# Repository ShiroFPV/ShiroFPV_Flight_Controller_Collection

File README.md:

# ShiroFPV Flight Controller Collection

Open-source FPV flight controller hardware — schematic, PCB layout, symbols and
firmware target, all published in full.

Designed in KiCad, targeted at Betaflight, and licensed so it stays open.

More at **[shirofpv.com/flight-controller](https://shirofpv.com/flight-controller)**

## Boards

| Board | Size | MCU | Analog OSD | Status |
|---|---|---|---|---|
| [**V1** `SFVPF435`](V1_30x30_SFVPF435/) | 30.5 × 30.5 | AT32F435RGT7 | ✅ AT7456 | Released |
| [**V2** `SFVPF435`](V2_20x20_SFVPF435/) | 20.5 × 20.5 | AT32F435, 48-pin | ❌ digital only | 🚧 In development |

---

## V1 — `SFVPF435` (30.5 × 30.5)

| | |
|---|---|
| **MCU** | Artery AT32F435RGT7, up to 288 MHz |
| **Gyro** | ICM-20602 |
| **Baro** | BME280 |
| **OSD** | AT7456 |
| **Blackbox** | 16 Mb onboard flash |
| **USB** | USB-C |
| **Mount** | 30.5 × 30.5 mm standard stack |
| **Firmware** | Betaflight |

### Layout

```
V1_30x30_SFVPF435/
├─ Shematic/          hardware sources — CERN-OHL-S v2
│  ├─ ShiroFPV_Flight_Controller.kicad_sch    schematic
│  ├─ ShiroFPV_Flight_Controller.kicad_pcb    PCB layout
│  ├─ All_Own_Symbols.kicad_sym               custom symbols
│  ├─ All_Own_Symbols.pretty/                 custom footprints
│  └─ .glb                                    3D model
└─ Release/           firmware — GPL-3.0-or-later
   ├─ config.h                                Betaflight target config
   └─ SFPVF435V1.hex                          compiled firmware
```

> Note: `Shematic/` is a typo for `Schematic/` kept as-is so existing links and
> clones don't break.

---

## V2 — `SFVPF435` (20 × 20) — coming soon

A smaller board for builds a 30.5 stack won't fit. Decided so far:

| | |
|---|---|
| **MCU** | AT32F435, 48-pin package |
| **Mount** | 20 × 20 mm |
| **Analog OSD** | none — digital video only |
| **Firmware** | Betaflight |

Dropping the analog OSD chip is what buys the space. Everything else — gyro,
baro, blackbox, UART count, power stage — is still being worked out.

Details in [`V2_20x20_SFVPF435/`](V2_20x20_SFVPF435/).

---

## Datasheets

Artery's documentation is not redistributed here — it is their copyright.
Download it from the source:

- **AT32F435** — [product page](https://www.arterychip.com/en/product/AT32F435.jsp)
  (datasheet + reference manual)
- **AT32F437** — [product page](https://www.arterychip.com/en/product/AT32F437.jsp)

---

## Building one

The design files are complete — schematic, layout, custom symbols and
footprints. Open `ShiroFPV_Flight_Controller.kicad_pro` in KiCad 8 or newer,
export gerbers, and send them to whichever fab you like.

Flash `SFPVF435V1.hex` with the Betaflight Configurator, or build from the
Betaflight sources using `config.h` as the target definition.

It flies. Mostly.

---

## Licence

Two licences, because there are two kinds of work here. Both copyleft.

| Part | Licence |
|---|---|
| Hardware design (`Shematic/`) | [CERN-OHL-S v2](LICENSE) |
| Firmware (`Release/`) | [GPL-3.0-or-later](V1_30x30_SFVPF435/Release/LICENSE) |

**Short version:** use it, modify it, build it, sell it. If you distribute a
modified version, publish your sources under the same licence. You can profit
from this design — you just can't close it.

Full detail and reasoning in **[LICENSING.md](LICENSING.md)**.

---

## Contributing

Issues and pull requests welcome — improvements, fixes, or a revision of your
own. Contributions are accepted under the same licences as above.

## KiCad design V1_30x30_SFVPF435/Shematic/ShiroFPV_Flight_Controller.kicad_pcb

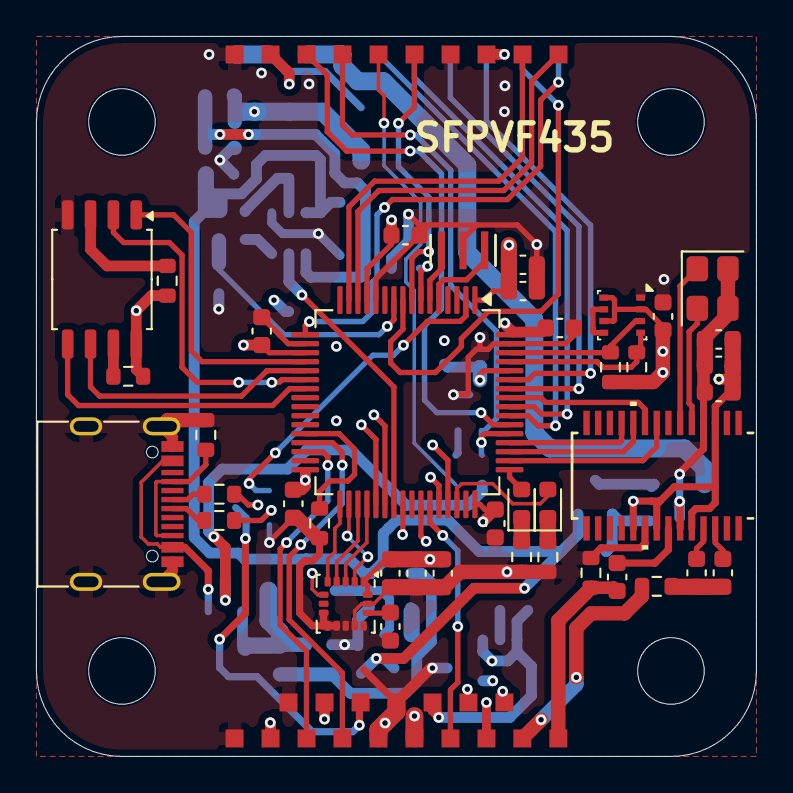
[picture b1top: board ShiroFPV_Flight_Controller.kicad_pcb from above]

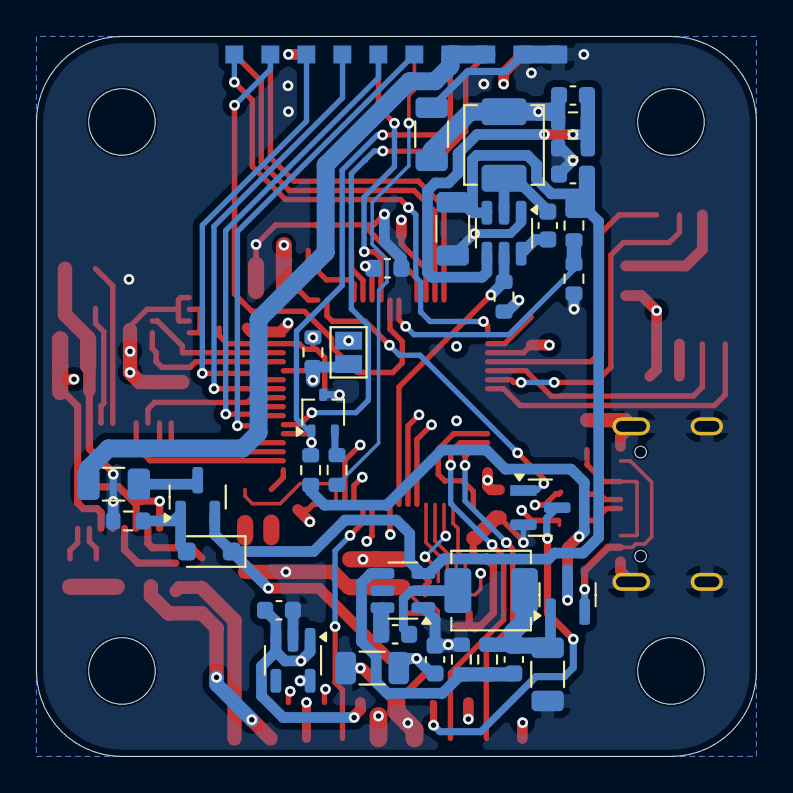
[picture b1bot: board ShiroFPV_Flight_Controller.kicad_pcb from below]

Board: 4 copper layers, 40.0 x 40.0 mm, 112 parts (45 on the bottom side), 79 nets.

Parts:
C1, C2, C4, C6, C7, C10, C11, C12, C13, C15, C16, C20, C23, C25, C26, C27, C28, C29: 100nF; C_0603_1608Metric
C3: 10nF; C_0603_1608Metric
C5, C31: 1uF; C_0603_1608Metric
C8, C9: 47uF; C_0603_1608Metric
C14, C38: 10uF; C_1206_3216Metric
C17: 100pF; C_0603_1608Metric
C18, C19: 47uF; C_1206_3216Metric
C22: 150pF; C_0603_1608Metric
C32: CSTCE8M00G52-R0; 8MHz-Osciallator.kicad_sym
C39: 2.2uF; C_0603_1608Metric
D1: MM3Z10VT1G; D_SOD-323_HandSoldering
D2: LED Blue; LED_0603_1608Metric
D3: LED Yellow; LED_0603_1608Metric
D4: PMEG4005CT,215; SOT-23
F1: Fuse; Fuse_1206_3216Metric
J1, J2, J46: GND; TestPoint_Pad_1.0x1.0mm_No_Silkscreen
J3, J4: VBAT; TestPoint_Pad_1.0x1.0mm_No_Silkscreen
J5: M1; TestPoint_Pad_1.0x1.0mm_No_Silkscreen
J6: M2; TestPoint_Pad_1.0x1.0mm_No_Silkscreen
J7: M3; TestPoint_Pad_1.0x1.0mm_No_Silkscreen
J8: M4; TestPoint_Pad_1.0x1.0mm_No_Silkscreen
J9: CUR; TestPoint_Pad_1.0x1.0mm_No_Silkscreen
J10: TLM; TestPoint_Pad_1.0x1.0mm_No_Silkscreen
J11: Video_Out; TestPoint_Pad_1.0x1.0mm_No_Silkscreen
J12: Video_IN; TestPoint_Pad_1.0x1.0mm_No_Silkscreen
J13: 5V3; TestPoint_Pad_1.0x1.0mm_No_Silkscreen
J14: RX3; TestPoint_Pad_1.0x1.0mm_No_Silkscreen
J15: TX3; TestPoint_Pad_1.0x1.0mm_No_Silkscreen
J16: GND3; TestPoint_Pad_1.0x1.0mm_No_Silkscreen
J17: 5V4; TestPoint_Pad_1.0x1.0mm_No_Silkscreen
J18: RX4; TestPoint_Pad_1.0x1.0mm_No_Silkscreen
J19: TX4; TestPoint_Pad_1.0x1.0mm_No_Silkscreen
J20: GND4; TestPoint_Pad_1.0x1.0mm_No_Silkscreen
J24: +5V; TestPoint_Pad_1.0x1.0mm_No_Silkscreen
J25: RSSI; TestPoint_Pad_1.0x1.0mm_No_Silkscreen
J26: GND5; TestPoint_Pad_1.0x1.0mm_No_Silkscreen
J29: SBUS; TestPoint_Pad_1.0x1.0mm_No_Silkscreen
J30: 5V5; TestPoint_Pad_1.0x1.0mm_No_Silkscreen
J31: RX5; TestPoint_Pad_1.0x1.0mm_No_Silkscreen
J32: TX5; TestPoint_Pad_1.0x1.0mm_No_Silkscreen
J33: RX6; TestPoint_Pad_1.0x1.0mm_No_Silkscreen
J34: 5V6; TestPoint_Pad_1.0x1.0mm_No_Silkscreen
J35: GND6; TestPoint_Pad_1.0x1.0mm_No_Silkscreen
J36: TX6; TestPoint_Pad_1.0x1.0mm_No_Silkscreen
J37: 10V; TestPoint_Pad_1.0x1.0mm_No_Silkscreen
J38: RX1; TestPoint_Pad_1.0x1.0mm_No_Silkscreen
J39: TX1; TestPoint_Pad_1.0x1.0mm_No_Silkscreen
J40: GND1; TestPoint_Pad_1.0x1.0mm_No_Silkscreen
J42: B-; TestPoint_Pad_1.0x1.0mm_No_Silkscreen
JP1: SolderJumper_2_Open; SolderJumper-2_P1.3mm_Open_Pad1.0x1.5mm
L1: 10uH; L_APV_APH0412
L2: 15uH; L_APV_APH0412
P1: USB_C_Plug_USB2.0; USB_C_Receptacle_G-Switch_GT-USB-7010ASV
Q1: AO3401A; SOT-23
Q2: AO3400A; SOT-23
Q3: BC817W; SOT-323_SC-70
R1, R7, R11: 100K; R_0603_1608Metric
R2: 12.3K; R_0603_1608Metric
R3, R4: 75R; R_0603_1608Metric
R5, R6, R9, R10, R19, R20: 10K; R_0603_1608Metric
R8: 6.2K; R_0603_1608Metric
R12, R13: 22R; R_0603_1608Metric
R14: 5.1K; R_0603_1608Metric
R15, R16: 150R; R_0603_1608Metric
R17, R29: 2.2K; R_0603_1608Metric
R21: 2K; R_0603_1608Metric
R22: 4.7K; R_0603_1608Metric
R27: 18K; R_0603_1608Metric
U1: AT32F435RGT7; LQFP-64_10x10mm_P0.5mm
U3: ICM-20602; LGA-16_3x3mm_P0.5mm_LayoutBorder3x5y
U4: BME280; Bosch_LGA-8_2.5x2.5mm_P0.65mm_ClockwisePinNumbering
U5: TPS54302; SOT-23-6
U6: TPS54302DDCR; SOT-23-6
U7: RT9013-33GB; SOT-23-5
U8: W25Q128JVS; SOIC-8_5.3x5.3mm_P1.27mm
U10: AT7456
Y2: 27MHz; Crystal_SMD_3225-4Pin_3.2x2.5mm

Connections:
9V_Enable: R9.2, U1.39 (PC8), U6.5 (EN)
+3.3V: C3.1, C6.2, C10.1, C23.1, C25.1, C26.1, C27.1, C28.1, C29.1, C31.1, C39.1, JP1.1 (A), R9.1, R17.1, R19.1, R20.2, R29.1, U1.1 (VBAT), U1.13 (VDDA), U1.19 (VDD), U1.32 (VDD), U1.48 (VDD), U1.64 (VDD), U3.1 (VDDIO), U3.16 (VDD), U4.2 (CSB), U4.6 (VDDIO), U4.8 (VDD), U7.5 (VOUT), U8.8 (VCC)
+5V: C5.1, C7.2, C12.2, C13.1, D4.3, J13.1 (Pin_1_1), J17.1 (Pin_1_1), J24.1 (Pin_1_1), J30.1 (Pin_1_1), J34.1 (Pin_1_1), R10.1, U7.1 (VIN), U7.3 (ON/~OFF), U10.3 (DVDD), U10.19 (*RESET), U10.21 (AVDD), U10.24 (PVDD)
+5V_BEC: C17.1, C18.1, D4.1, L1.2, R1.1
+10V: C19.1, C22.1, J37.1 (Pin_1_1), L2.2, R7.1
ADC_CURRENT: J9.1 (Pin_1_1), U1.9 (PC1)
ADC_RSSI: J25.1 (Pin_1_1), U1.8 (PC0)
ADC_VBAT: R21.1, R27.2, U1.10 (PC2)
BEEPER: Q2.2 (G), U1.2 (PC13)
BEEPER_B-: J42.1 (Pin_1_1), Q2.1 (D)
BOOT0: JP1.2 (B), R5.1, U1.60 (BOOT0)
BOOT1: R6.1, U1.28 (PB2)
FLASH_CS: U1.20 (PA4), U8.1 (~CS)
FLASH_MISO: U1.22 (PA6), U8.2 (DO/IO_{1})
FLASH_MOSI: U1.23 (PA7), U8.5 (DI/IO_{0})
FLASH_SCK: U1.21 (PA5), U8.6 (CLK)
GND: C1.1, C3.2, C4.1, C5.2, C6.1, C7.1, C10.2, C12.1, C13.2, C14.2, C15.2, C18.2, C19.2, C20.2, C23.2, C25.2, C26.2, C27.2, C28.2, C29.2, C31.2, C32.2, C38.2, C39.2, J1.1 (Pin_1_1), J2.1 (Pin_1_1), J16.1 (Pin_1_1), J20.1 (Pin_1_1), J26.1 (Pin_1_1), J35.1 (Pin_1_1), J40.1 (Pin_1_1), J46.1 (Pin_1_1), P1.A1 (GND), P1.A12 (GND), P1.B1 (GND), P1.B12 (GND), P1.S1 (SHIELD), Q2.3 (S), Q3.3 (E), R2.1, R4.2, R5.2, R6.2, R8.2, R11.2, R14.1, R15.2, R16.2, R21.2, U1.12 (VSSA), U1.18 (VSS), U1.63 (VSS), U3.8 (FSYNC), U3.9 (GND), U3.10 (GND), U3.11 (GND), U3.12 (GND), U3.13 (GND), U3.15 (GND), U4.1 (GND), U4.5 (SDO), U4.7 (GND), U5.1 (GND), U6.1 (GND), U7.2 (GND), U8.4 (GND), U10.4 (DGND), U10.20 (AGND), U10.23 (PGND), Y2.3, Y2.4
GYRO_CS: U1.33 (PB12), U3.5 (~CS)
GYRO_INIT: U1.40 (PC9), U3.6 (INT)
GYRO_SCK: U1.34 (PB13), U3.2 (SCL/SPC)
GYRO_SDA: U1.36 (PB15), U3.3 (SDA/SDI)
GYRO_SDO: U1.35 (PB14), U3.4 (SAO/SD0)
I2C_SCL: R17.2, U1.61 (PB8), U4.4 (SCK)
I2C_SDA: R29.2, U1.62 (PB9), U4.3 (SDI)
LEDSTATUS0: D2.2 (A), U1.49 (PA14)
LEDSTATUS1: D3.2 (A), U1.46 (PA13)
M1: J5.1 (Pin_1_1), U1.55 (PB3)
M2: J6.1 (Pin_1_1), U1.56 (PB4)
M3: J7.1 (Pin_1_1), U1.58 (PB6)
M4: J8.1 (Pin_1_1), U1.59 (PB7)
unnamed: C8.2, C9.2, R3.1
unnamed: D1.2 (A), Q1.2 (G), R11.1
unnamed: D2.1 (K), R16.1
unnamed: D3.1 (K), R15.1
unnamed: P1.A5 (CC), P1.B5 (VCONN), R14.2
unnamed: P1.A6 (D+), R12.1
unnamed: P1.A7 (D-), R13.1
unnamed: F1.2, Q1.1 (D)
unnamed: Q3.2 (B), R22.2
unnamed: C4.2, U1.7 (NRST)
unnamed: C1.2, U3.14 (REGOUT)
unnamed: C2.2, U5.6 (BOOT)
unnamed: C17.2, R1.2, R2.2, U5.4 (FB)
unnamed: C2.1, L1.1, U5.2 (SW)
unnamed: C16.2, U6.6 (BOOT)
unnamed: C22.2, R7.2, R8.1, U6.4 (FB)
unnamed: C16.1, L2.1, U6.2 (SW)
unnamed: R20.1, U8.7 (~HOLD/~RESET/IO_{3})
unnamed: R19.2, U8.3 (~WP/IO_{2})
unnamed: U10.5 (CLKIN), Y2.2
unnamed: C9.1, U10.25 (SAG)
unnamed: C11.1, U10.22 (VIN)
unnamed: C8.1, U10.26 (VOUT)
unnamed: U10.6 (XFB), Y2.1
OSC_IN: C32.3, U1.5 (PH0)
OSC_OUT: C32.1, U1.6 (PH1)
OSD_CS: U1.50 (PA15), U10.8 (*CS)
OSD_MISO: U1.52 (PC11), U10.11 (SDOUT)
OSD_MOSI: U1.57 (PB5), U10.9 (SDIN)
OSD_SCK: U1.51 (PC10), U10.10 (SCLK)
SBUS: J29.1 (Pin_1_1), R22.1
UART1RX: J38.1 (Pin_1_1), U1.43 (PA10)
UART1TX: J39.1 (Pin_1_1), U1.42 (PA9)
UART2RX: J10.1 (Pin_1_1), U1.17 (PA3)
UART3RX: J14.1 (Pin_1_1), U1.30 (PB11)
UART3TX: J15.1 (Pin_1_1), U1.29 (PB10)
UART4RX: J18.1 (Pin_1_1), U1.15 (PA1)
UART4TX: J19.1 (Pin_1_1), U1.14 (PA0)
UART5RX: J31.1 (Pin_1_1), U1.54 (PD2)
UART5TX: J32.1 (Pin_1_1), Q3.1 (C), R10.2, U1.53 (PC12)
UART6RX: J33.1 (Pin_1_1), U1.38 (PC7)
UART6TX: J36.1 (Pin_1_1), U1.37 (PC6)
USBD+: R12.2, U1.45 (PA12)
USBD-: R13.2, U1.44 (PA11)
VBAT: F1.1, J3.1 (Pin_1_1), J4.1 (Pin_1_1)
VBUS: D4.2, P1.A4 (VBUS), P1.A9 (VBUS), P1.B4 (VBUS), P1.B9 (VBUS)
VIN: C14.1, C15.1, C20.1, C38.1, D1.1 (K), Q1.3 (S), R27.1, U5.3 (VIN), U6.3 (VIN)
V_IN: C11.2, J12.1 (Pin_1_1), R4.1
V_OUT: J11.1 (Pin_1_1), R3.2

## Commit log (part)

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2026-05-19 V1(2)
2026-05-19 V1(3)
2026-06-26 Add KiCad project files and 3D model
    Add initial project artifacts for V1_30x30_SFVPF435: include a .glb 3D model, a .kicad_prl project preferences file, and KiCad lock files. Also add macOS .DS_Store files. Tweak the board file (ShiroF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
